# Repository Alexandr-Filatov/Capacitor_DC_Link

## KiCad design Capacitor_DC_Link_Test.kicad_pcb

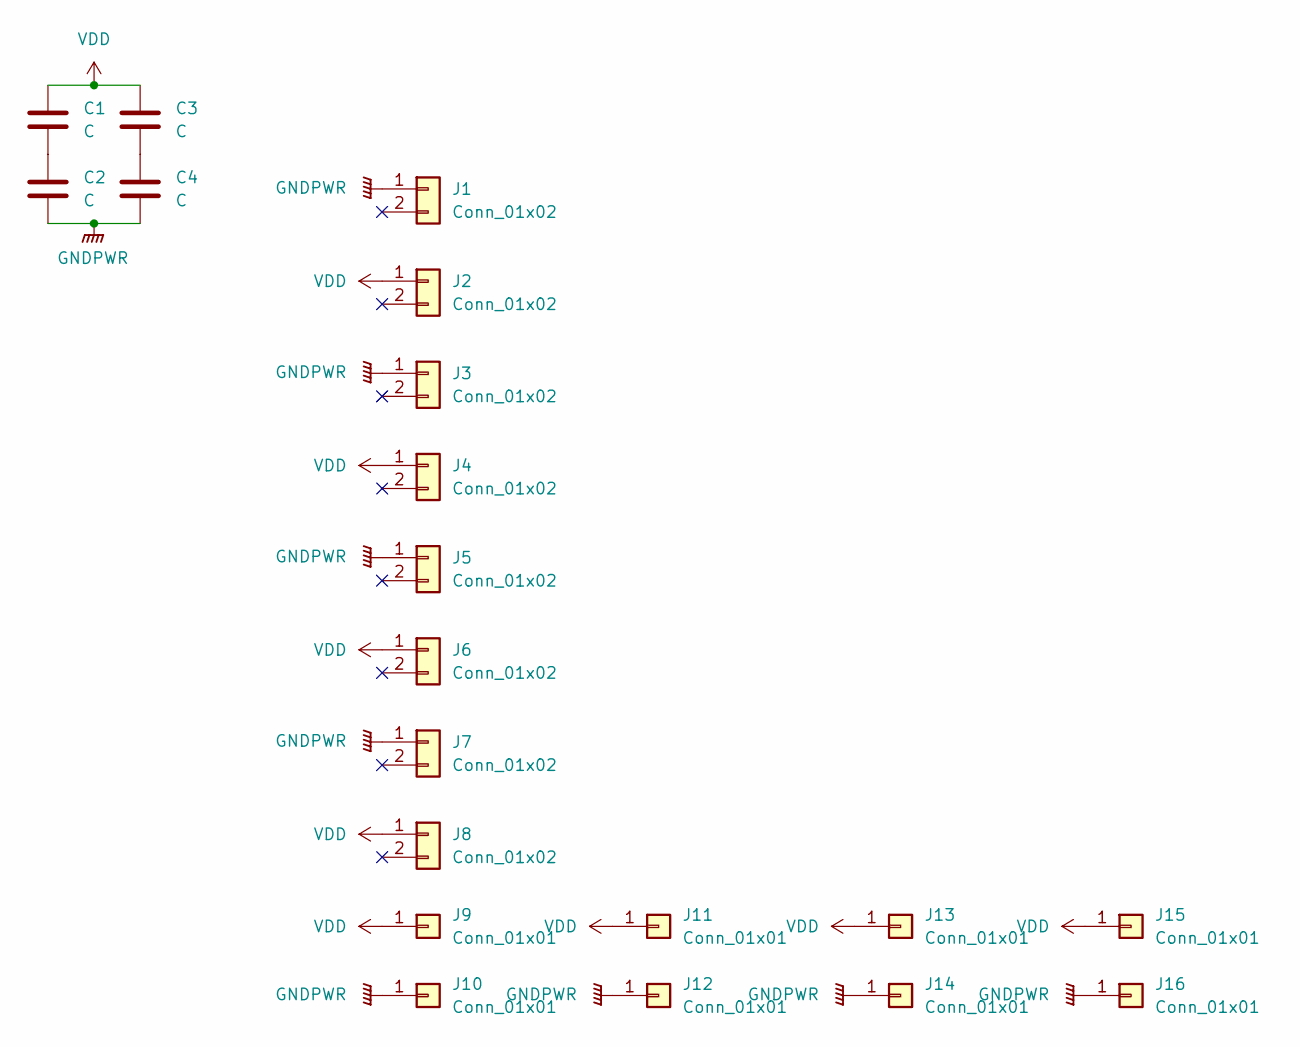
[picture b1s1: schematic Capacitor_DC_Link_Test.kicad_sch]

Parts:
C1, C2, C3, C4: C; Capacitor_22x36.5x31.5
J1, J3, J5, J7: Conn_01x02; Low_IN
J2, J4, J6, J8: Conn_01x02; High_IN
J9, J10, J11, J12, J13, J14, J15, J16: Conn_01x01; Bush_5x3

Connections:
GNDPWR: C2.2, C4.2, J1.1, J3.1, J5.1, J7.1, J10.1, J12.1, J14.1, J16.1
unnamed: C1.2, C2.1
unnamed: C3.2, C4.1
VDD: C1.1, C3.1, J2.1, J4.1, J6.1, J8.1, J9.1, J11.1, J13.1, J15.1

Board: 2 copper layers, 20 parts (0 on the bottom side), 4 nets, no tracks yet.

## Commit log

2025-12-04 zero commit
2025-12-04 VER1.0: поставил нужные конденсаторы
2025-12-08 VER1.0: добавил модели конденсаторов
2025-12-09 VER1.0: расширил плату
2025-12-17 VER1.0: добавил вводные шины
2025-12-18 VER1.0: изменил шины
2026-01-22 VER1.0: добавил чертеж шины
